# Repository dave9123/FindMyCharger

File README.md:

# FindMyCharger

<p align="center">
	
	<br><a href="./zine.pdf">View Magazine</a> - <a href="#bom">View BOM</a>
</p>

FindMyCharger is a smart powerbank with finding capabilities so you don't have to worry where did you place your powerbank!

## Why?

I've been forgetting things a lot, also it can be part of aging (or ekhem ekhem sleep depreviation) which then causes people to lose their stuff. I don't hope for it, but there might be a chance that someone would steal your bag, and this just gives you a piece of mind!

## How it Works

IP5353 handles powerbank-like controls for charging and charging other devices, E104-BT5005A (based on nRF52805) transmits BLE packets which can be used with [Apple's FindMy](https://github.com/dchristl/macless-haystack) and/or [Google's Find Hub](https://github.com/leonboe1/GoogleFindMyTools).

## Build Instructions

You can either:
- PCBA
- Manual Solder 

Afterwards, you'll need:

1. Everything from [BOM](./BOM.md) (pick PCBA/detailed depending on your usecase)
2. SWD Debugging Interface
3. 4x Jumper Wires

(additional if manual solder)

4. Soldering Iron
5. Solder

Steps:
1. Print the PCB from [pcb/jlcpcb/production_files/GERBER-FindMyCharger.zip](./pcb/jlcpcb/production_files/GERBER-FindMyCharger.zip)
2. Solder the components based on [BOM](#BOM) or PCBA with [JLCPCB CPL](./pcb/jlcpcb/production_files/CPL-FindMyCharger.csv) and [JLCPCB BOM](./pcb/jlcpcb/production_files/BOM-FindMyCharger.csv)
3. 3D print the casing in [CAD folder](./cad/components/)
4. Place the battery on the bottom holder

|  |  |
| :------------------------------------------: | :---------------------------------------------------------------: |

5. Solder battery with wires (to be soldered on the PCB)
6. Place the bottom holder dock

|  |  |
| :---------------------------------------------------------------: | :---------------------------------------------------------------------: |

7. Place and fit the PCB on the dock

|  |  |
| :---------------------------------------------------------------------: | :----------------------------------------------------------: |

8. Build and flash the [firmware](#firmware) by connecting a SWD debugger to (SW)DIO, (SW)CLK, and GND
9. Place the top and screw it with M2x6

|  |  |
| ------------------------------------------------------------ | --------------------------------------------------------- |

## Firmware

The firmware for FindMyCharger is using [Macless Haystack](https://github.com/dchristl/macless-haystack), a framework for custom FindMy network without having to own a Mac.

Macless Haystack is included in this repository as a submodule under [firmware/macless-haystack](../firmware/macless-haystack/)

### Prerequisites (guide below to install):

1. nRF Connect SDK
2. https://github.com/dchristl/macless-haystack repo or current (follow guide below)
3. Python 2/3 (with pip), download [here](https://www.python.org/downloads/)
4. Pip package ["cryptography"](http://pypi.org/project/cryptography) -- `pip install cryptography`
5. Visual Studio Code, download [here](https://code.visualstudio.com/)
6. CMake, download [here](https://cmake.org/download/) or `sudo apt install cmake`

 ### Clone repository along with submodules:

7. Install the ["nRF Connect for VS Code" VSCode Extension here](https://marketplace.visualstudio.com/items?itemName=nordic-semiconductor.nrf-connect)

2. Open the nRF Connect extension on the left bar

3. Click on "Install SDK" and pick the latest version

4. Click on "Install Toolchain" and pick the latest version

5. Wait for it to finish installing

### Clone repository along with submodules

```
git clone --recurse-submodules https://github.com/dave9123/FindMyCharger

cd FindMyCharger/firmware/macless-haystack

git -C macless-haystack submodule update --init --remote --recursive
```

Then, you'll need to download the firmware (nrf52_firmware.bin) at Macless Haystack releases [here](https://github.com/dchristl/macless-haystack/releases) or build your own:
```
cd firmware/macless-haystack

py generate_keys.py # Note the output folder from the output "Output will be written to {OUTPUT_FOLDER}"

cd firmware/nrf5x

NRF_MODEL=nrf52 BOARD=BOARD_E104BT5032A make build

make patch
```

### Afterwards, update the finding public key

note: use Git Bash on Windows

Replace "PREFIX_keyfile" with the path to your generated public key (stored in the ../../output folder)

```
export LC_CTYPE=C

xxd -p -c 100000 PREFIX_keyfile | xxd -r -p | dd of=nrf52_firmware.bin skip=1 bs=1 seek=$(grep -oba OFFLINEFINDINGPUBLICKEYHERE! nrf52_firmware.bin | cut -d ':' -f 1) conv=notrunc
```

### Patch and deploy firmware

```
openocd -f interface/stlink.cfg -c "transport select hla_swd" -f target/nrf52.cfg -c "init; halt; nrf5 mass_erase; program nrf52_firmware.bin verify; reset run; exit"
```

The complete guide on setting Macless Haystack can be found [here](https://github.com/dchristl/macless-haystackhttps://github.com/dchristl/macless-haystack)!

## Casing

|  |  |
| :------------------------------------: | :--------------------------------------: |

I'm honestly really proud of how it ends up, especially the sliding mechanism which makes everything easier to place

|  |  |
| :-----------------------------------------------------------------: | :------------------------------------------------------: |

The holes on the side is for the cable to passthrough either the GND or positive side of the battery to be soldered onto the PCB

## Schematics

Detailed components list used can be found in the [BOM section](#bom)

[View PDF](./assets/schematics.pdf)

## PCB

|                    Design                     |                 Rendered                 |
| :-------------------------------------------: | :--------------------------------------: |
|  |  |

[View PDF](./assets/pcb.pdf)

Footprints used:
1. Battery Solder Pad - `Connector_Wire:SolderWire-0.1sqmm_1x02_P3.6mm_D0.4mm_OD1mm`
2. Capacitor 100nF - `Capacitor_SMD:C_0402_1005Metric`
3. Capacitor 2.2uF - `Capacitor_SMD:C_0603_1608Metric`
4. Capacitor 22uF - `Capacitor_SMD:C_0805_2012Metric`
5. LED `LED_SMD:LED_0603_1608Metric`
6. USB C Receptacle - `footprints:USB-C-SMD_TYPE-C16PIN` (imported from EasyEDA, included under `pcb/libraries/footprints.pretty)
7. Inductor 2.2uH - `footprints:IND-SMD_L6.0-W6.0_CHILISIN_HPPC06030` (imported from EasyEDA, included under `pcb/libraries/footprints.pretty`)
8. Resistor 10kΩ - `Resistor_SMD:R_0402_1005Metric`
9. Resistor 100Ω - `Resistor_SMD:R_0402_1005Metric`
10. 90deg Tactile Button - `footprints:KEY-TH_SKHLLDA010` (imported from EasyEDA, included under `pcb/libraries/footprints.pretty`)
11. Test Points - `TestPoint:TestPoint_Pad_D2.5mm`
12. IP5353 (charging) - `footprints:QFN-32_L5.0-W5.0-P0.50-TL-EP3.5` (imported from EasyEDA, included under `pcb/libraries/footprints.pretty`)
13. E104-BT5005A (BLE) - `footprints:BULETM-SMD_E104-BT5005A` (imported from EasyEDA, included under `pcb/libraries/footprints.pretty`)
14. 3.3V Voltage Regulator - `footprints:SOT-89-3_L4.5-W2.5-P1.50-LS4.2-BR` (imported from EasyEDA, included under `pcb/libraries/footprints.pretty`)

## BOM

### PCBA

| Item                | Quantity | Total Cost         | Order                                                                                                                                             |
| ------------------- | -------- | ------------------ | ------------------------------------------------------------------------------------------------------------------------------------------------- |
| M2x6 Screw          | 4        | Rp5.000<br>~$0.28  | https://www.tokopedia.com/archive-lapaktukang/10pcs-baut-hitam-m2-m2x3-m2x4-m2x5-m2x6-m2x7-m2x8-m2x10-1731486102402008940                         |
| 18650 Li-on Battery | 1        | Rp27.500<br>~$1.54 | https://www.tokopedia.com/nayfastore/baterai-isi-ulang-baterai-tipe-lithium-ion-18650-butontop-3000mah-3-7v-isi-2-pcs-1731453786169640483         |
| Casing 3D Print     | 1        | Rp44.384<br>~$2.49 |                                                                                                                          |
| PCBA                | 1        | $45.63             |                                                                                                                             |
| Wire                | 2        | Rp4.000<br>~$0.22  | https://www.tokopedia.com/cncstorebandung/kabel-tunggal-mini-wire-single-core-tinned-cu-permeter-hitam-merah-hijau-kuning-putih-0-6mm-hitam-27149 |
|                     |          |                    |                                                                                                                                                   |
| Total               |          | $48.4              |                                                                                                                                                   |

### Detailed

| Item                            | Quantity | Total Cost         | Order                                                                                                                                             |
| ------------------------------- | -------- | ------------------ | ------------------------------------------------------------------------------------------------------------------------------------------------- |
| M2x6 Screw                      | 4        | Rp5.000<br>~$0.28  | https://www.tokopedia.com/archive-lapaktukang/10pcs-baut-hitam-m2-m2x3-m2x4-m2x5-m2x6-m2x7-m2x8-m2x10-1731486102402008940                         |
| 18650 Li-on Battery             | 1        | Rp27.500<br>~$1.54 | https://www.tokopedia.com/nayfastore/baterai-isi-ulang-baterai-tipe-lithium-ion-18650-butontop-3000mah-3-7v-isi-2-pcs-1731453786169640483         |
| Casing 3D Print                 | 1        | Rp44.384<br>~$2.49 |                                                                                                                          |
| Wire                            | 2        | Rp4.000<br>~$0.22  | https://www.tokopedia.com/cncstorebandung/kabel-tunggal-mini-wire-single-core-tinned-cu-permeter-hitam-merah-hijau-kuning-putih-0-6mm-hitam-27149 |
| Resistor 100Ω 0402              | 2        | $0.002             | C25076 (JLCPCB)                                                                                                                                   |
| Capacitor 100nF 0402            | 5        | $0.04              | C307331 (JLCPCB)                                                                                                                                  |
| Resistor 10k 0402               | 1        | $0.015             | C25744 (JLCPCB)                                                                                                                                   |
| Thermistor 10k 3380K 0402       | 1        | $0.008             | C29553871 (JLCPCB)                                                                                                                                |
| Capacitor 2.2uF 0603            | 3        | $0.027             | C23630 (JLCPCB)                                                                                                                                   |
| Inductor 2.2uH SMD 6.0x6.0mm    | 1        | $0.24              | C285900 (JLCPCB)                                                                                                                                  |
| USB C Receptacle 16P            | 1        | $0.065             | C393939 (JLCPCB)                                                                                                                                  |
| Capacitor 22uF 0805             | 7        | $0.665             | C45783 (JLCPCB)                                                                                                                                   |
| LED White 0603                  | 4        | $0.048             | C2290 (JLCPCB)                                                                                                                                    |
| 90deg Tactile Button SKHLLDA010 | 1        | $0.239             | C125032 (JLCPCB)                                                                                                                                  |
| Bluetooth Module E104-BT5005A   | 1        | $3.67              | C2874127 (JLCPCB)                                                                                                                                 |
| 3.3V LDO HT7533                 | 1        | $0.125             | C14289 (JLCPCB)                                                                                                                                   |
| Charging Module IP5353          | 1        | $0.999             | C46550234 (JLCPCB)                                                                                                                                |
| 4-layer PCB                     | 1        | $2.1               | JLCPCB                                                                                                                                            |
|                                 |          |                    |                                                                                                                                                   |
| Total                           |          | $12.55             |                                                                                                                                                   |
note: JLCPCB components are for PCBA only and total cost doesn't factor extended ($3) cost nor PCBA fees

note 2: price does not include shipping, taxes, customs (import) nor Minimum Order Quantity (MOQ)

*price as of 27/06/2026 03:22 GMT+7*

## Credits

Software used:
- [KiCad](https://kicad.org/)
- [Autodesk Fusion](https://www.autodesk.com/education/edu-software/fusion)

- 18650 Battery 3D model: https://grabcad.com/library/cell-18650-1
- Macless Haystack: https://github.com/dchristl/macless-haystack

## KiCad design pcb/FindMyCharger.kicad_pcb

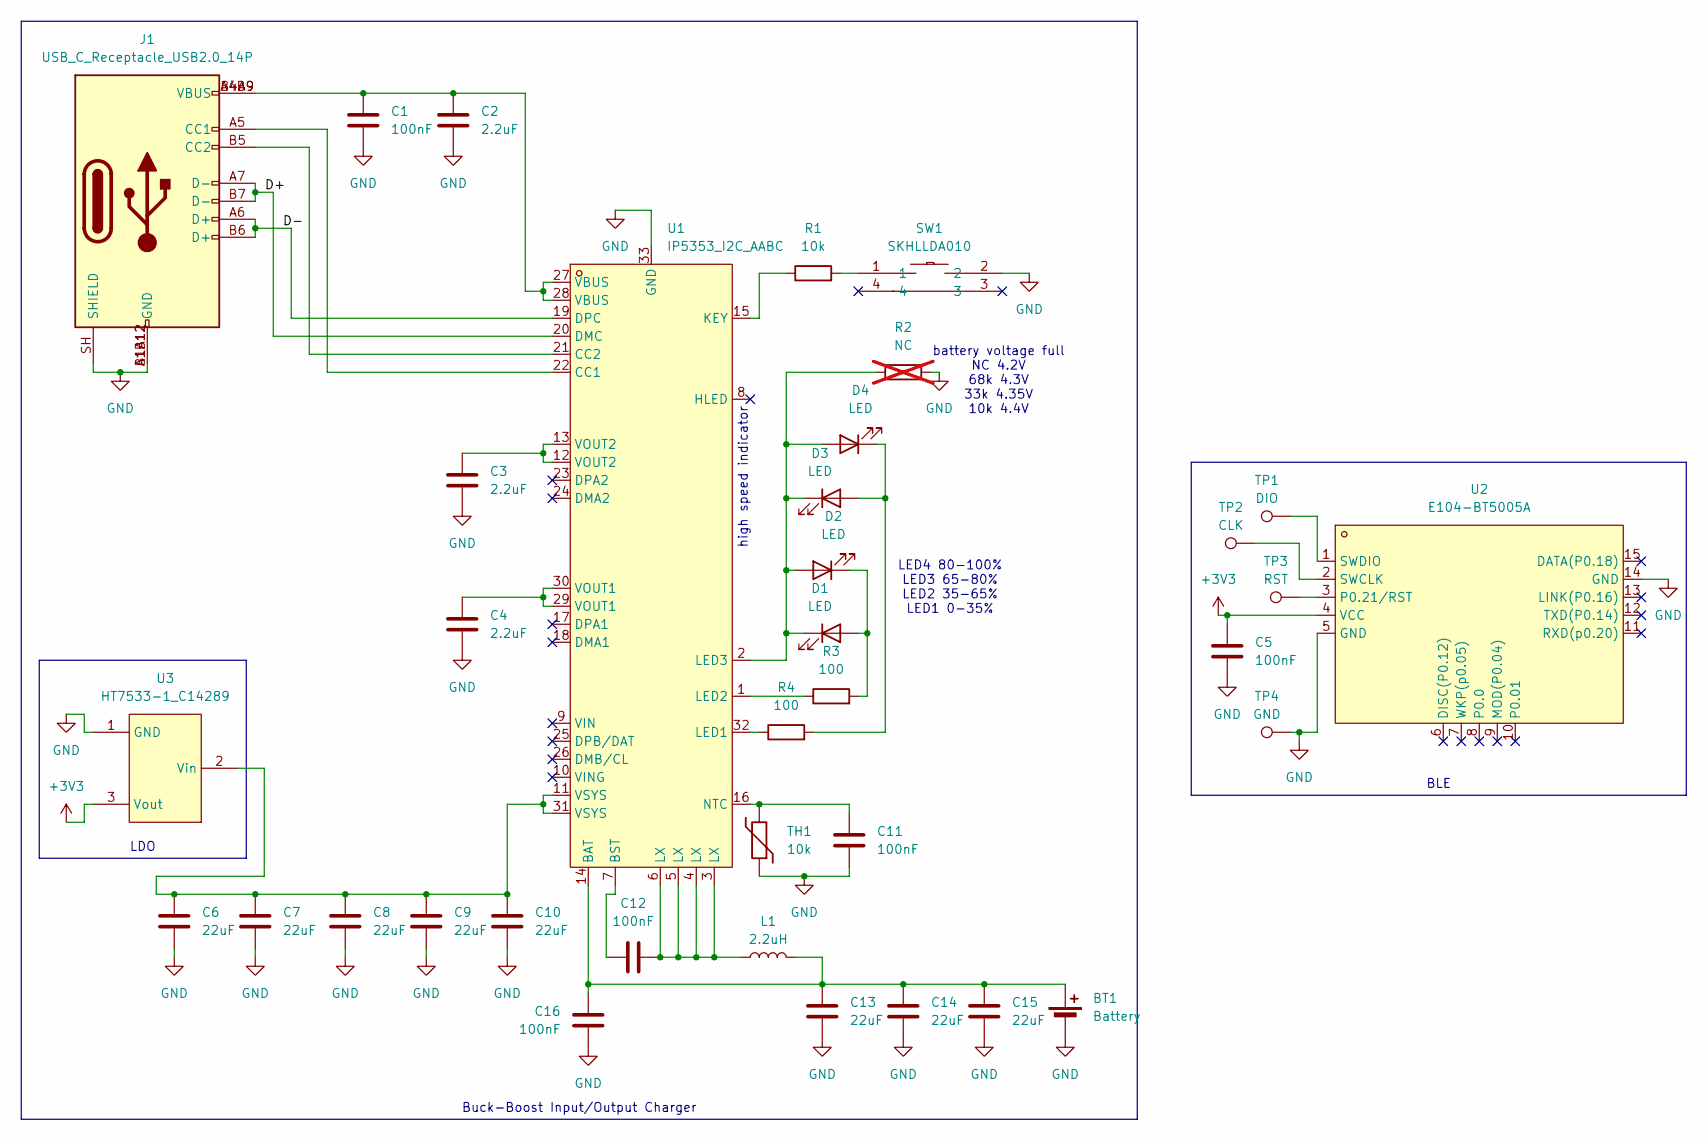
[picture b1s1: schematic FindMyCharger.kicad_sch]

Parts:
BT1: Battery; SolderWire-0.1sqmm_1x02_P3.6mm_D0.4mm_OD1mm
C1, C5, C11, C12, C16: 100nF; C_0402_1005Metric; LCSC Part C307331
C2, C3, C4: 2.2uF; C_0603_1608Metric; LCSC Part C23630
C6, C7, C8, C9, C10, C13, C14, C15: 22uF; C_0805_2012Metric; LCSC Part C45783
D1, D2, D3, D4: LED; LED_0603_1608Metric; LCSC Part C2290
J1: USB_C_Receptacle_USB2.0_14P; USB-C-SMD_TYPE-C16PIN; LCSC Part C393939
L1: 2.2uH; IND-SMD_L6.0-W6.0_CHILISIN_HPPC06030; LCSC Part C285900
R1: 10k; R_0402_1005Metric; LCSC Part C25744
R2: NC; R_0603_1608Metric; not fitted
R3, R4: 100; R_0402_1005Metric; LCSC Part C25076
SW1: SKHLLDA010; KEY-TH_SKHLLDA010; LCSC Part C125032
TH1: 10k; R_0402_1005Metric; LCSC Part C41417281
TP1: DIO; TestPoint_Pad_D2.5mm
TP2: CLK; TestPoint_Pad_D2.5mm
TP3: RST; TestPoint_Pad_D2.5mm
TP4: GND; TestPoint_Pad_2.5x2.5mm
U1: IP5353_I2C_AABC; QFN-32_L5.0-W5.0-P0.50-TL-EP3.5; LCSC Part C46550234
U2: E104-BT5005A; BULETM-SMD_E104-BT5005A; LCSC Part C2874127
U3: HT7533-1_C14289; SOT-89-3_L4.5-W2.5-P1.50-LS4.2-BR; LCSC Part C14289

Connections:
+3V3: C5.1, U2.4 (VCC), U3.3 (Vout); also elsewhere on the board
/D+: J1.A7 (D-), J1.B7 (D-), U1.20 (DMC)
/D-: J1.A6 (D+), J1.B6 (D+), U1.19 (DPC)
GND: BT1.1 (-), C1.2, C2.2, C3.2, C4.2, C5.2, C6.2, C7.2, C8.2, C9.2, C10.2, C11.2, C13.2, C14.2, C15.2, C16.2, J1.A1B12 (GND), J1.B1A12 (GND), J1.SH (SHIELD), R2.1, SW1.2, TH1.1, TP4.1 (1_1), U1.33 (GND), U2.5 (GND), U2.14 (GND), U3.1 (GND)
unnamed: BT1.2 (+), C13.1, C14.1, C15.1, C16.1, L1.2, U1.14 (BAT)
unnamed: C1.1, C2.1, J1.A4B9 (VBUS), J1.B4A9 (VBUS), U1.27 (VBUS), U1.28 (VBUS)
unnamed: C3.1, U1.12 (VOUT2), U1.13 (VOUT2)
unnamed: C4.1, U1.29 (VOUT1), U1.30 (VOUT1)
unnamed: C12.2, L1.1, U1.3 (LX), U1.4 (LX), U1.5 (LX), U1.6 (LX)
unnamed: D1.2 (A), D2.1 (K), R3.2
unnamed: D1.1 (K), D2.2 (A), D3.1 (K), D4.2 (A), R2.2, U1.2 (LED3)
unnamed: D3.2 (A), D4.1 (K), R4.2
unnamed: J1.A5 (CC1), U1.22 (CC1)
unnamed: J1.B5 (CC2), U1.21 (CC2)
unnamed: R1.2, SW1.1
unnamed: C12.1, U1.7 (BST)
unnamed: R1.1, U1.15 (KEY)
unnamed: R4.1, U1.32 (LED1)
unnamed: R3.1, U1.1 (LED2)
unnamed: C11.1, TH1.2, U1.16 (NTC)
unnamed 20: TP3.1, U2.3 (P0.21/RST); also elsewhere on the board
unnamed 21: TP2.1, U2.2 (SWCLK); also elsewhere on the board
unnamed 22: TP1.1, U2.1 (SWDIO); also elsewhere on the board
unnamed: C6.1, C7.1, C8.1, C9.1, C10.1, U1.11 (VSYS), U1.31 (VSYS), U3.2 (Vin)

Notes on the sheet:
high speed indicator
LED4 80-100% LED3 65-80% LED2 35-65% LED1 0-35%
battery voltage full NC 4.2V 68k 4.3V 33k 4.35V 10k 4.4V
BLE
LDO
Buck-Boost Input/Output Charger

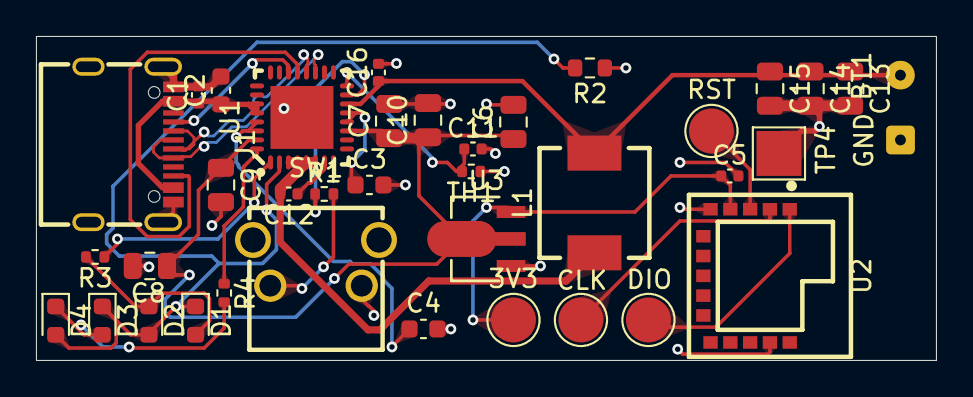
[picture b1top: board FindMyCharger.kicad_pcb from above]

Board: 4 copper layers, 50.0 x 18.0 mm, 37 parts (0 on the bottom side), 24 nets.

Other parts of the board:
3V3: 3V3; TestPoint_Pad_D2.5mm
CLK: CLK; TestPoint_Pad_D2.5mm
DIO: DIO; TestPoint_Pad_D2.5mm
RST: RST; TestPoint_Pad_D2.5mm

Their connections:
+3V3: 3V3.1 (1_1); also elsewhere on the board
unnamed 20: RST.1 (1_1); also elsewhere on the board
unnamed 21: CLK.1 (1_1); also elsewhere on the board
unnamed 22: DIO.1 (1_1); also elsewhere on the board

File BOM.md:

# BOM

## PCBA

| Item                | Quantity | Total Cost         | Order                                                                                                                                             |
| ------------------- | -------- | ------------------ | ------------------------------------------------------------------------------------------------------------------------------------------------- |
| M2x6 Screw          | 4        | Rp5.000<br>~$0.28  | https://www.tokopedia.com/archive-lapaktukang/10pcs-baut-hit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                         |
| 18650 Li-on Battery | 1        | Rp27.500<br>~$1.54 | https://www.tokopedia.com/nayfastore/baterai-isi-ulang-bater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         |
| Casing 3D Print     | 1        | Rp44.384<br>~$2.49 | ![](./assets/3dprint.jpg)                                                                                                                         |
| PCBA                | 1        | $45.63             | ![](./assets/pcba.jpg)                                                                                                                            |
| Wire                | 2        | Rp4.000<br>~$0.22  | https://www.tokopedia.com/cncstorebandung/kabel-tunggal-mini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 |
|                     |          |                    |                                                                                                                                                   |
| Total               |          | $48.4              |                                                                                                                                                   |


## Detailed

| Item                            | Quantity | Total Cost         | Order                                                                                                                                             |
| ------------------------------- | -------- | ------------------ | ------------------------------------------------------------------------------------------------------------------------------------------------- |
| M2x6 Screw                      | 4        | Rp5.000<br>~$0.28  | https://www.tokopedia.com/archive-lapaktukang/10pcs-baut-hit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                         |
| 18650 Li-on Battery             | 1        | Rp27.500<br>~$1.54 | https://www.tokopedia.com/nayfastore/baterai-isi-ulang-bater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         |
| Casing 3D Print                 | 1        | Rp44.384<br>~$2.49 | ![](./assets/3dprint.jpg)                                                                                                                         |
| Wire                            | 2        | Rp4.000<br>~$0.22  | https://www.tokopedia.com/cncstorebandung/kabel-tunggal-mini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 |
| Resistor 100Ω 0402              | 2        | $0.002             | C25076 (JLCPCB)                                                                                                                                   |
| Capacitor 100nF 0402            | 5        | $0.04              | C307331 (JLCPCB)                                                                                                                                  |
| Resistor 10k 0402               | 1        | $0.015             | C25744 (JLCPCB)                                                                                                                                   |
| Thermistor 10k 3380K 0402       | 1        | $0.008             | C29553871 (JLCPCB)                                                                                                                                |
| Capacitor 2.2uF 0603            | 3        | $0.027             | C23630 (JLCPCB)                                                                                                                                   |
| Inductor 2.2uH SMD 6.0x6.0mm    | 1        | $0.24              | C285900 (JLCPCB)                                                                                                                                  |
| USB C Receptacle 16P            | 1        | $0.065             | C393939 (JLCPCB)                                                                                                                                  |
| Capacitor 22uF 0805             | 7        | $0.665             | C45783 (JLCPCB)                                                                                                                                   |
| LED White 0603                  | 4        | $0.048             | C2290 (JLCPCB)                                                                                                                                    |
| 90deg Tactile Button SKHLLDA010 | 1        | $0.239             | C125032 (JLCPCB)                                                                                                                                  |
| Bluetooth Module E104-BT5005A   | 1        | $3.67              | C2874127 (JLCPCB)                                                                                                                                 |
| 3.3V LDO HT7533                 | 1        | $0.125             | C14289 (JLCPCB)                                                                                                                                   |
| Charging Module IP5353          | 1        | $0.999             | C46550234 (JLCPCB)                                                                                                                                |
| PCB                             | 1        | $2.1               | JLCPCB                                                                                                                                            |
|                                 |          |                    |                                                                                                                                                   |
| Total                           |          | $12.55             |                                                                                                                                                   |
note: JLCPCB components are for PCBA only and total cost doesn't factor extended ($3) cost nor PCBA fees


*price as of 27/06/2026 03:22 GMT+7*

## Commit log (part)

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2025-11-23 replace PD module
2025-11-23 to do list so I don't forget ;)
2025-11-24 KiCad files init
2025-11-24 Added nRF54 IC onto schematics
2025-11-25 Included footprint
2025-12-01 update todo list
2025-12-01 clean .gitignore and included buck boost
2025-12-01 started to connect batteries
2025-12-02 starting to connect cells to BMS
2025-12-02 moved a bit into the paper
2025-12-05 vault backup: 2025-12-05 22:39:07
2025-12-06 finished making the battery pack schematics :)
2025-12-11 added usb c connector
2025-12-12 replace bms
2025-12-12 replaced bms
2025-12-12 connected moisture detection
2025-12-15 is it just me or I can't just make my mind up
2025-12-27 Updated libraries
2025-12-27 Connected quite some stuff, still a long way to go
2025-12-28 Finished input charge
2025-12-28 Updated README and connected more stuff
2025-12-28 more stuff
2025-12-30 protection IC
2025-12-30 Finished BMS
2025-12-30 Finished BMS handling, kinda
2025-12-31 Finished circuit
2026-01-01 left to include test pads for comms
2026-01-22 updating to tps25772-q1 from *762* to "save" space
2026-01-23 more i2c
2026-01-23 remove old charging, gotta setup new one
2026-01-24 more filling
2026-01-25 schematics done
2026-01-25 returning to 762 bc 772 only supports as source, not sink
2026-01-25 added capacitors and inductors as per nrf54 datasheet
2026-01-25 including some footprints
2026-02-01 connected antenna footprint
2026-03-24 some footprints assigment (incomplete)
2026-03-26 to do list update + capacitor footprints assigned
2026-03-27 update goals and todos
2026-03-27 include volts
2026-04-02 kicad 10 update + some power rating
2026-04-03 more pads n update todo
2026-04-03 move
2026-04-19 some esd
2026-04-19 more esd + research
2026-04-19 shield to gnd
2026-05-29 replace with non handsolder
2026-05-29 add 2010
2026-05-30 fix SNS power rating
2026-05-30 some stuf
2026-05-31 no handsolder
2026-06-07 return footprint
2026-06-08 update nrf54 footprints
2026-06-08 hide property
2026-06-08 config stuf
2026-06-09 stuf
2026-06-10 add drc pcb jlcpcb
2026-06-10 datasheet and sch changes
2026-06-11 more
2026-06-11 rm handsolder
2026-06-11 fixed metric
2026-06-11 fix metric removed bc of backup
2026-06-11 lots
2026-06-12 footprint
2026-06-12 padss
2026-06-12 update visibility
2026-06-13 tried fab plugin
2026-06-13 maaths
2026-06-13 more maht
2026-06-14 eeprom
2026-06-15 crystal
2026-06-16 update naming
2026-06-16 soic
2026-06-16 update thermal foldback
2026-06-18 tidy up
2026-06-18 renum
2026-06-19 inductor
2026-06-19 assign
2026-06-20 more part
2026-06-20 made to dsg
2026-06-20 updated footprint
2026-06-20 excl debug/pads from bom
2026-06-20 finished mapping
2026-06-20 pcbbb
2026-06-20 dumped
2026-06-20 rean
2026-06-20 firmware init
2026-06-20 route
2026-06-20 update firmware
2026-06-20 cleanup
2026-06-20 fixed bracket
2026-06-20 zine ref
2026-06-21 main cad
2026-06-23 add ble
2026-06-24 return
2026-06-25 footprint assignemnt done
2026-06-26 fix 3dmodels mapping
2026-06-26 updated bom
2026-06-27 fix via directly on component
2026-06-27 update zine
2026-06-27 forgot to connect nRST
2026-06-28 fixed drc
2026-06-28 updated docs, fixed naming
2026-06-28 add footprints list
2026-06-28 added spacing in-between images
2026-06-28 enhance why section
2026-06-28 updated bom url
2026-06-28 improve flashing clarity
